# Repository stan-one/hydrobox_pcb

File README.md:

# Hydrobox PCB
PCB files and schematic for the hydrobox project

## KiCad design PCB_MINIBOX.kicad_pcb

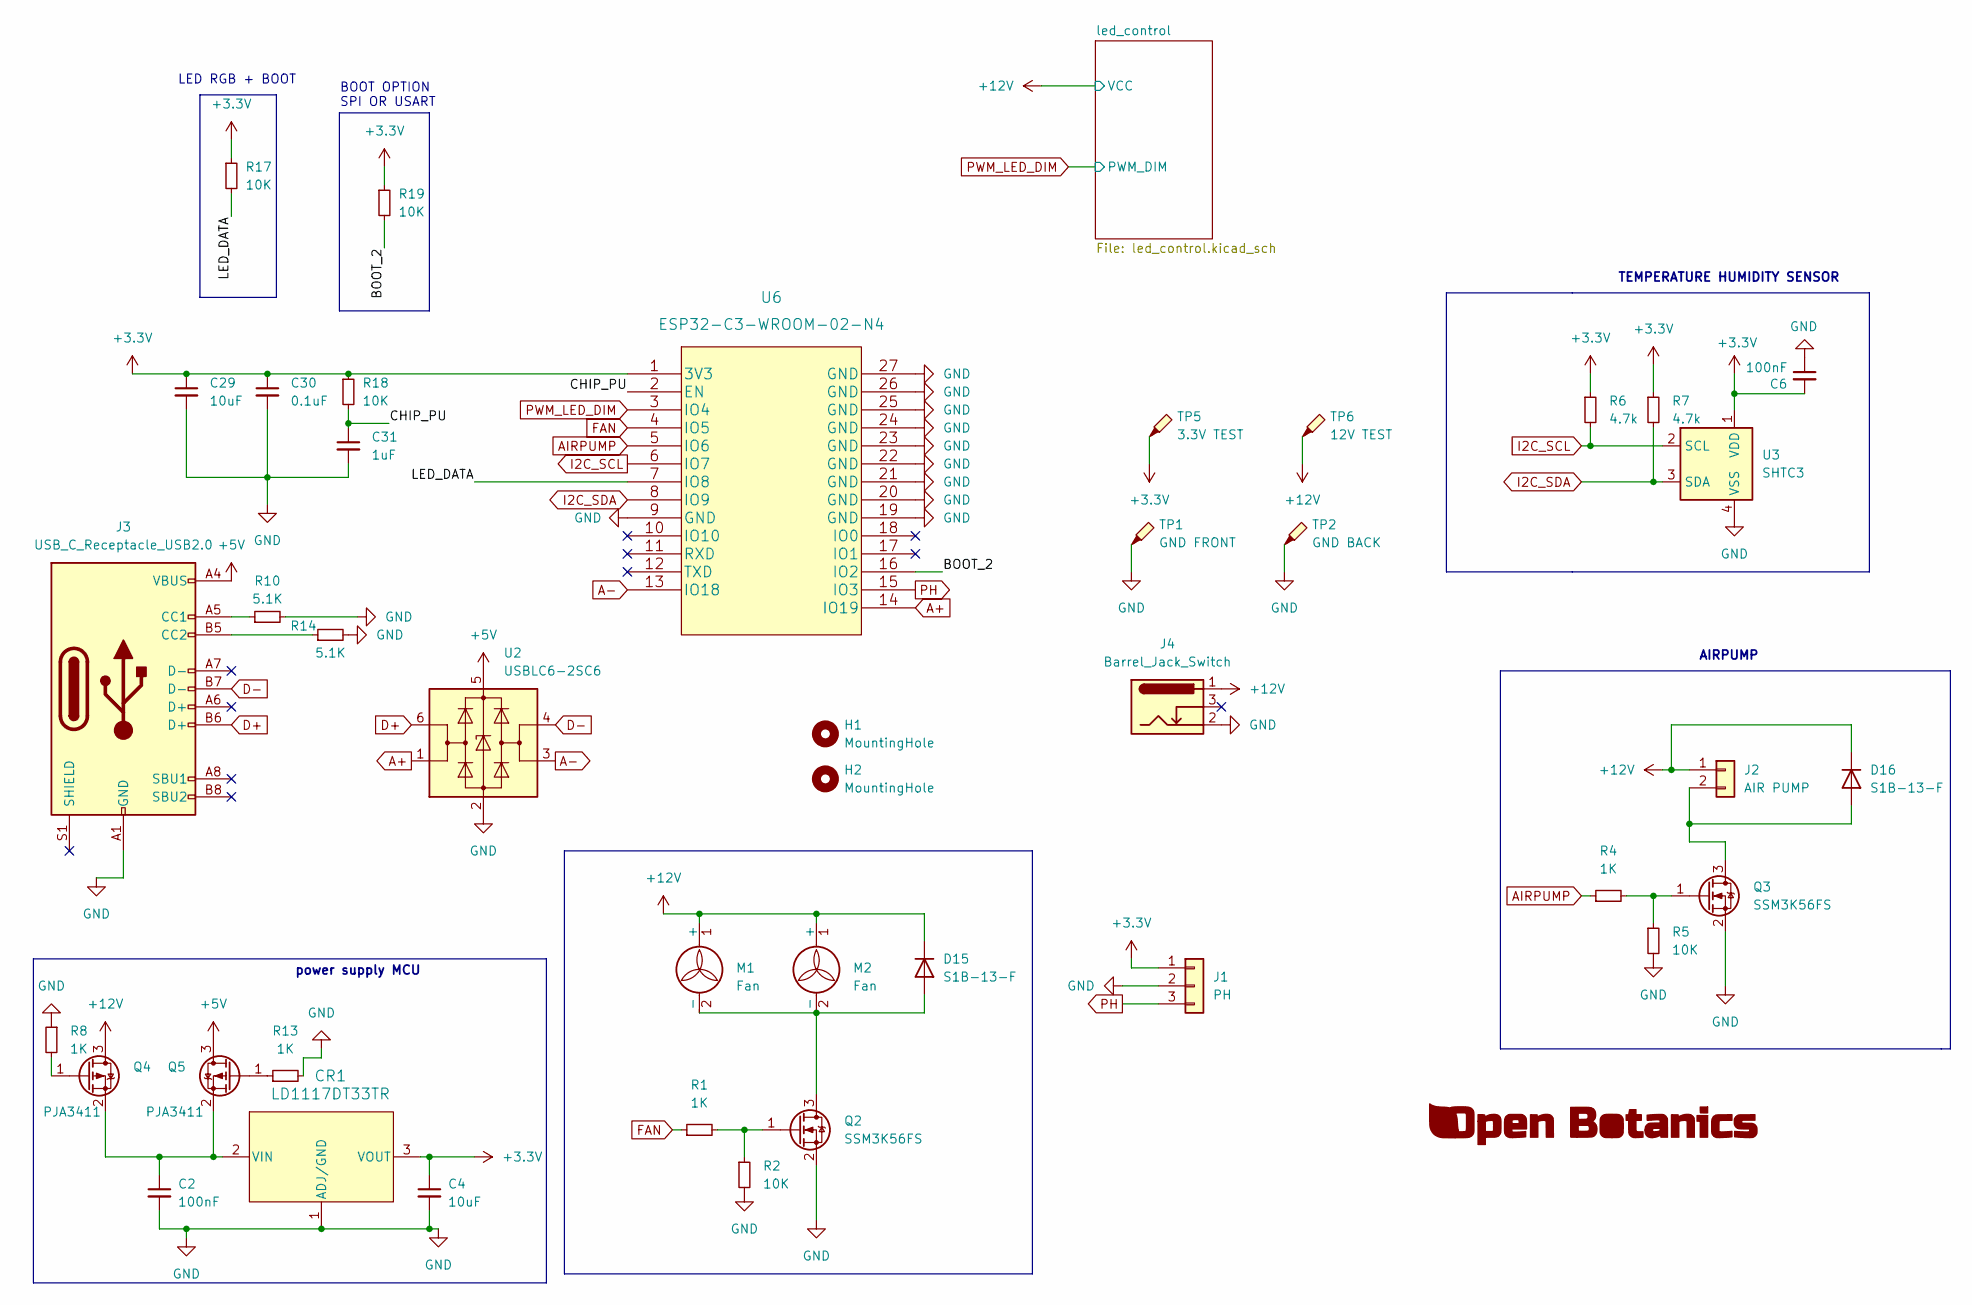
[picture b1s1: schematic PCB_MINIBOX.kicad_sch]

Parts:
C2, C6: 100nF; C_0603_1608Metric_Pad1.08x0.95mm_HandSolder
C4, C29: 10uF; C_0805_2012Metric_Pad1.18x1.45mm_HandSolder
C30: 0.1uF; C_0603_1608Metric_Pad1.08x0.95mm_HandSolder
C31: 1uF; C_0603_1608Metric_Pad1.08x0.95mm_HandSolder
CR1: LD1117DT33TR; TO-252-3_TabPin4
D15, D16: S1B-13-F; D_SMA
H1, H2: MountingHole; MountingHole_2.2mm_M2_Pad
J1: PH; PinHeader_1x03_P2.54mm_Horizontal
J2: AIR PUMP; PinHeader_1x02_P2.54mm_Horizontal
J3: USB_C_Receptacle_USB2.0; USB_C_Receptacle_HRO_TYPE-C-31-M-12
J4: Barrel_Jack_Switch; CUI_PJ-007
M1, M2: Fan; PinHeader_1x02_P2.54mm_Horizontal
Q2, Q3: SSM3K56FS; SOT-23
Q4, Q5: PJA3411; SOT-23
R1, R4, R8, R13: 1K; R_0603_1608Metric_Pad0.98x0.95mm_HandSolder
R2, R5, R17, R18, R19: 10K; R_0603_1608Metric_Pad0.98x0.95mm_HandSolder
R6, R7: 4.7k; R_0603_1608Metric_Pad0.98x0.95mm_HandSolder
R10, R14: 5.1K; R_0603_1608Metric
TP1: GND FRONT; TestPoint_Pad_D1.5mm
TP2: GND BACK; TestPoint_Pad_D1.5mm
TP5: 3.3V TEST; TestPoint_Pad_D1.5mm
TP6: 12V TEST; TestPoint_Pad_D1.5mm
U2: USBLC6-2SC6; SOT-23-6
U3: SHTC3; Sensirion_DFN-4-1EP_2x2mm_P1mm_EP0.7x1.6mm
U6: ESP32-C3-WROOM-02-N4

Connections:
+3.3V: C4.1, C6.2, C29.1, C30.1, CR1.3 (VOUT), J1.1, R6.1, R7.1, R17.1, R18.1, R19.1, TP5.1, U3.1 (VDD), U6.1 (3V3)
+5V: J3.A4 (VBUS), J3.A9 (VBUS), J3.B4 (VBUS), J3.B9 (VBUS), Q5.3 (D), U2.5 (VBUS)
+12V: D15.1 (K), D16.1 (K), J2.1, J4.1, M1.1 (+), M2.1 (+), Q4.3 (D), TP6.1; also elsewhere on the board
/BOOT_2: R19.2, U6.16 (IO2)
/CHIP_PU: C31.1, R18.2, U6.2 (EN)
/LED_DATA: R17.2, U6.7 (IO8)
A+: U2.1 (I/O1), U6.14 (IO19)
A-: U2.3 (I/O2), U6.13 (IO18)
AIRPUMP: R4.1, U6.5 (IO6)
D+: J3.B6 (D+), U2.6 (I/O1)
D-: J3.B7 (D-), U2.4 (I/O2)
FAN: R1.1, U6.4 (IO5)
GND: C2.2, C4.2, C6.1, C29.2, C30.2, C31.2, CR1.1 (ADJ/GND), J1.2, J3.A1 (GND), J3.A12 (GND), J3.B1 (GND), J3.B12 (GND), J4.2, Q2.2 (S), Q3.2 (S), R2.2, R5.2, R8.1, R10.2, R13.2, R14.2, TP1.1, TP2.1, U2.2 (GND), U3.4 (VSS), U6.9 (GND), U6.19 (GND), U6.20 (GND), U6.21 (GND), U6.22 (GND), U6.23 (GND), U6.24 (GND), U6.25 (GND), U6.26 (GND), U6.27 (GND); also elsewhere on the board
I2C_SCL: R6.2, U3.2 (SCL), U6.6 (IO7)
I2C_SDA: R7.2, U3.3 (SDA), U6.8 (IO9)
unnamed: C2.1, CR1.2 (VIN), Q4.2 (S), Q5.2 (S)
unnamed: D15.2 (A), M1.2 (-), M2.2 (-), Q2.3 (D)
unnamed: D16.2 (A), J2.2, Q3.3 (D)
unnamed: J3.A5 (CC1), R10.1
unnamed: J3.B5 (CC2), R14.1
unnamed: Q2.1 (G), R1.2, R2.1
unnamed: Q3.1 (G), R4.2, R5.1
unnamed: Q4.1 (G), R8.2
unnamed: Q5.1 (G), R13.1
PH: J1.3, U6.15 (IO3)
PWM_LED_DIM: U6.3 (IO4); also elsewhere on the board

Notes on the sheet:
BOOT OPTION SPI OR USART
LED RGB + BOOT
AIRPUMP
TEMPERATURE HUMIDITY SENSOR
power supply MCU

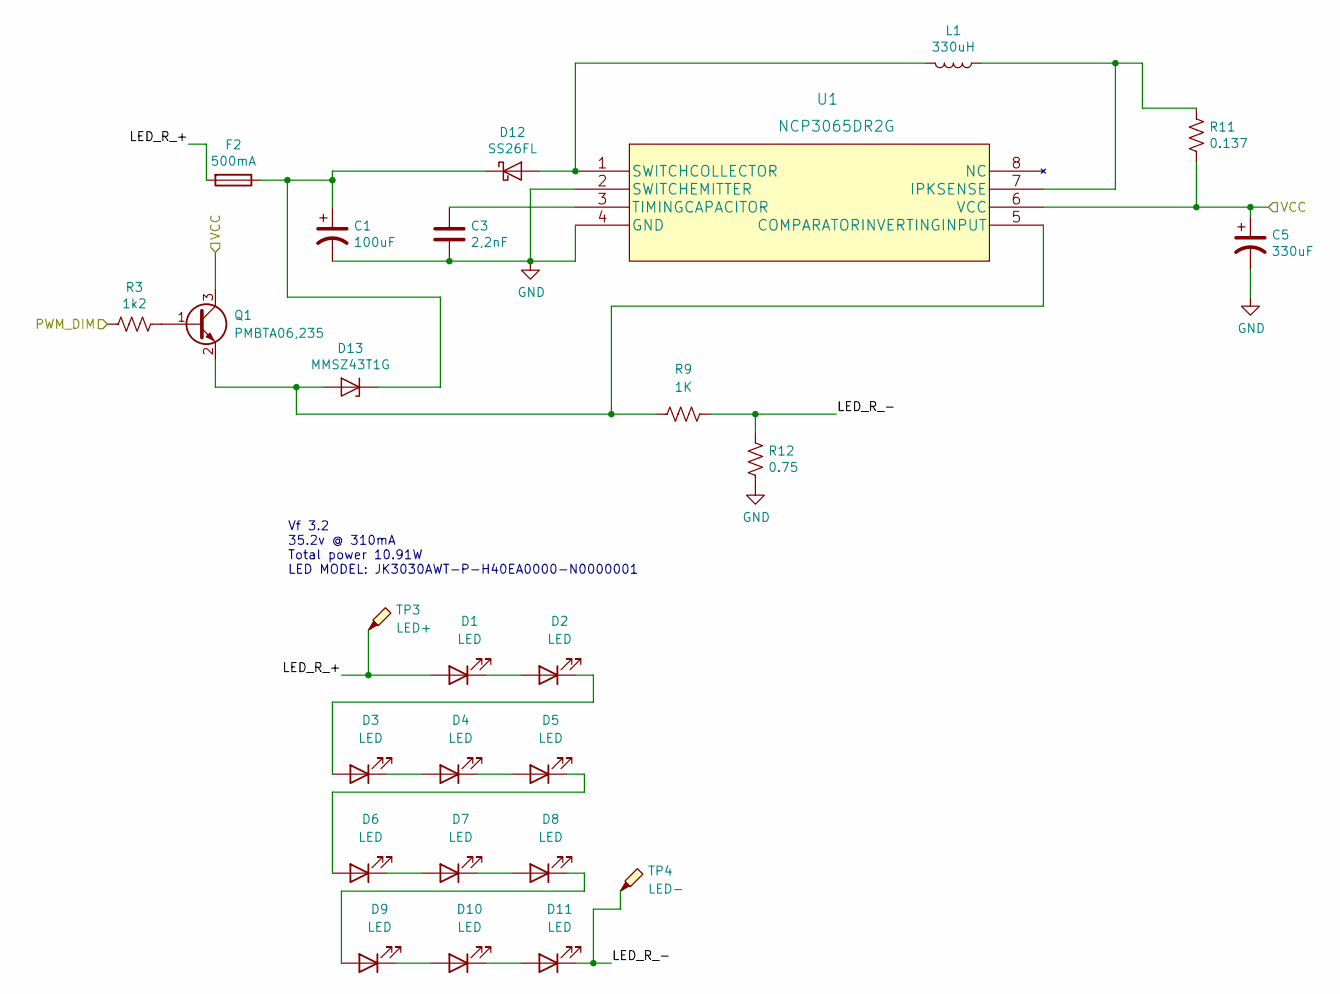
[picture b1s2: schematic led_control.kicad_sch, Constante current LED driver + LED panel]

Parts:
C1: 100uF; CP_Radial_D10.0mm_P5.00mm
C3: 2,2nF; C_0805_2012Metric_Pad1.18x1.45mm_HandSolder
C5: 330uF; CP_Radial_D10.0mm_P5.00mm
D1, D2, D3, D4, D5, D6, D7, D8, D9, D10, D11: LED; JK3030AWT-P-H40EA0000-N0000001
D12: SS26FL; D_SOD-123F
D13: MMSZ43T1G; D_SOD-123
F2: 500mA; Fuse_1206_3216Metric_Pad1.42x1.75mm_HandSolder
L1: 330uH; L_Radial_D10.0mm_P5.00mm_Fastron_07P
Q1: PMBTA06,235; SOT-23
R3: 1k2; R_0603_1608Metric_Pad0.98x0.95mm_HandSolder
R9: 1K; R_0603_1608Metric_Pad0.98x0.95mm_HandSolder
R11: 0.137; R_1210_3225Metric_Pad1.30x2.65mm_HandSolder
R12: 0.75; R_0805_2012Metric_Pad1.20x1.40mm_HandSolder
TP3: LED+; TestPoint_Pad_D1.5mm
TP4: LED-; TestPoint_Pad_D1.5mm
U1: NCP3065DR2G

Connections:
+12V: C5.1, Q1.3 (C), R11.2, U1.6 (VCC); also elsewhere on the board
/led_control/LED_R_+: D1.2 (A), F2.2, TP3.1
/led_control/LED_R_-: D11.1 (K), R9.2, R12.1, TP4.1
GND: C1.2, C3.2, C5.2, R12.2, U1.2 (SWITCHEMITTER), U1.4 (GND); also elsewhere on the board
unnamed: C1.1, D12.1 (K), D13.1 (K), F2.1
unnamed: C3.1, U1.3 (TIMINGCAPACITOR)
unnamed: D1.1 (K), D2.2 (A)
unnamed: D2.1 (K), D3.2 (A)
unnamed: D3.1 (K), D4.2 (A)
unnamed: D4.1 (K), D5.2 (A)
unnamed: D5.1 (K), D6.2 (A)
unnamed: D6.1 (K), D7.2 (A)
unnamed: D7.1 (K), D8.2 (A)
unnamed: D8.1 (K), D9.2 (A)
unnamed: D10.1 (K), D11.2 (A)
unnamed: D9.1 (K), D10.2 (A)
unnamed: D12.2 (A), L1.2, U1.1 (SWITCHCOLLECTOR)
unnamed: D13.2 (A), Q1.2 (E), R9.1, U1.5 (COMPARATORINVERTINGINPUT)
unnamed: L1.1, R11.1, U1.7 (IPKSENSE)
unnamed: Q1.1 (B), R3.1
PWM_LED_DIM: R3.2; also elsewhere on the board

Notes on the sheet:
Vf 3.2 35.2v @ 310mA Total power 10.91W LED MODEL: JK3030AWT-P-H40EA0000-N0000001

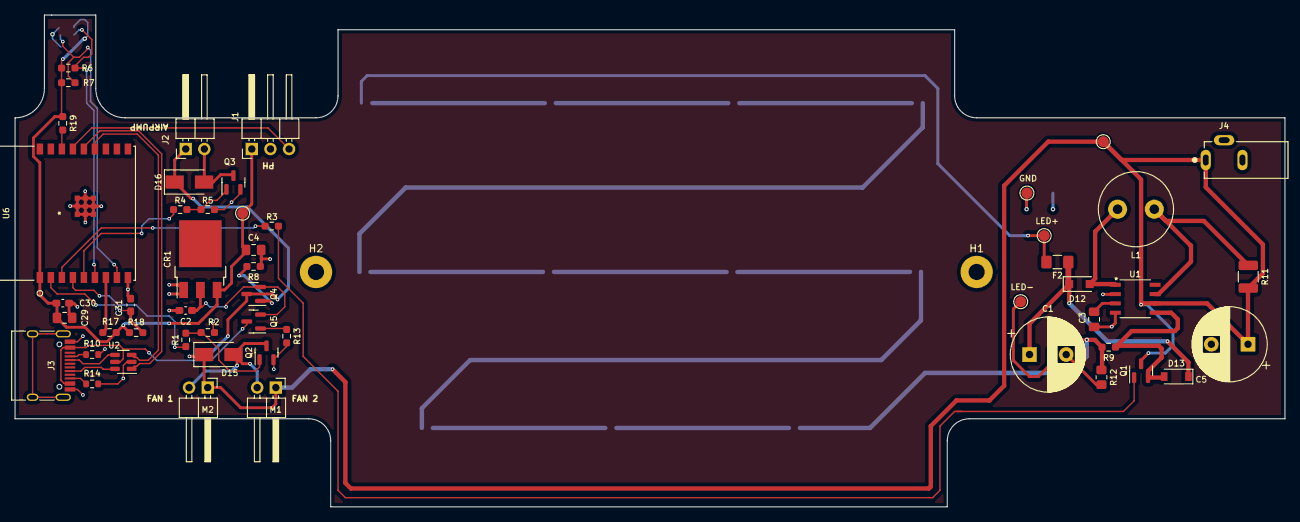
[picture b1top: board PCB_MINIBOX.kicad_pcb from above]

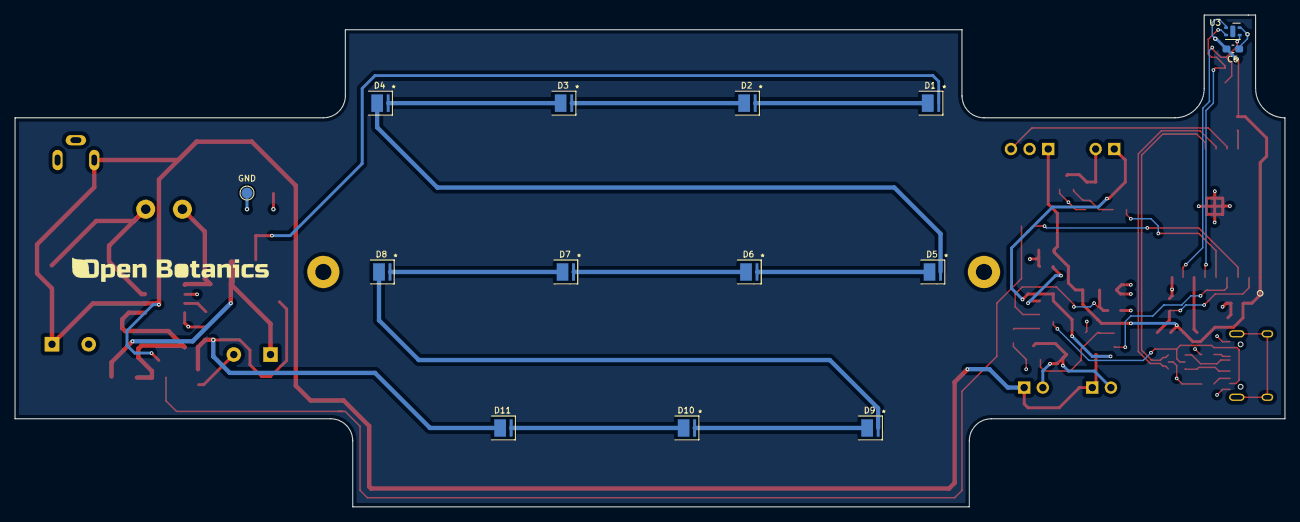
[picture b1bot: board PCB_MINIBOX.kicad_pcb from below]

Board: 4 copper layers, 173.0 x 67.0 mm, 67 parts (14 on the bottom side), 44 nets.

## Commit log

2023-02-12 Add files via upload
    Genesis
2023-02-12 Update README.md
    Inserted Images

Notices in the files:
parts and their libraries:
Copyright 2021 Accelerated Designs. All rights reserved.
